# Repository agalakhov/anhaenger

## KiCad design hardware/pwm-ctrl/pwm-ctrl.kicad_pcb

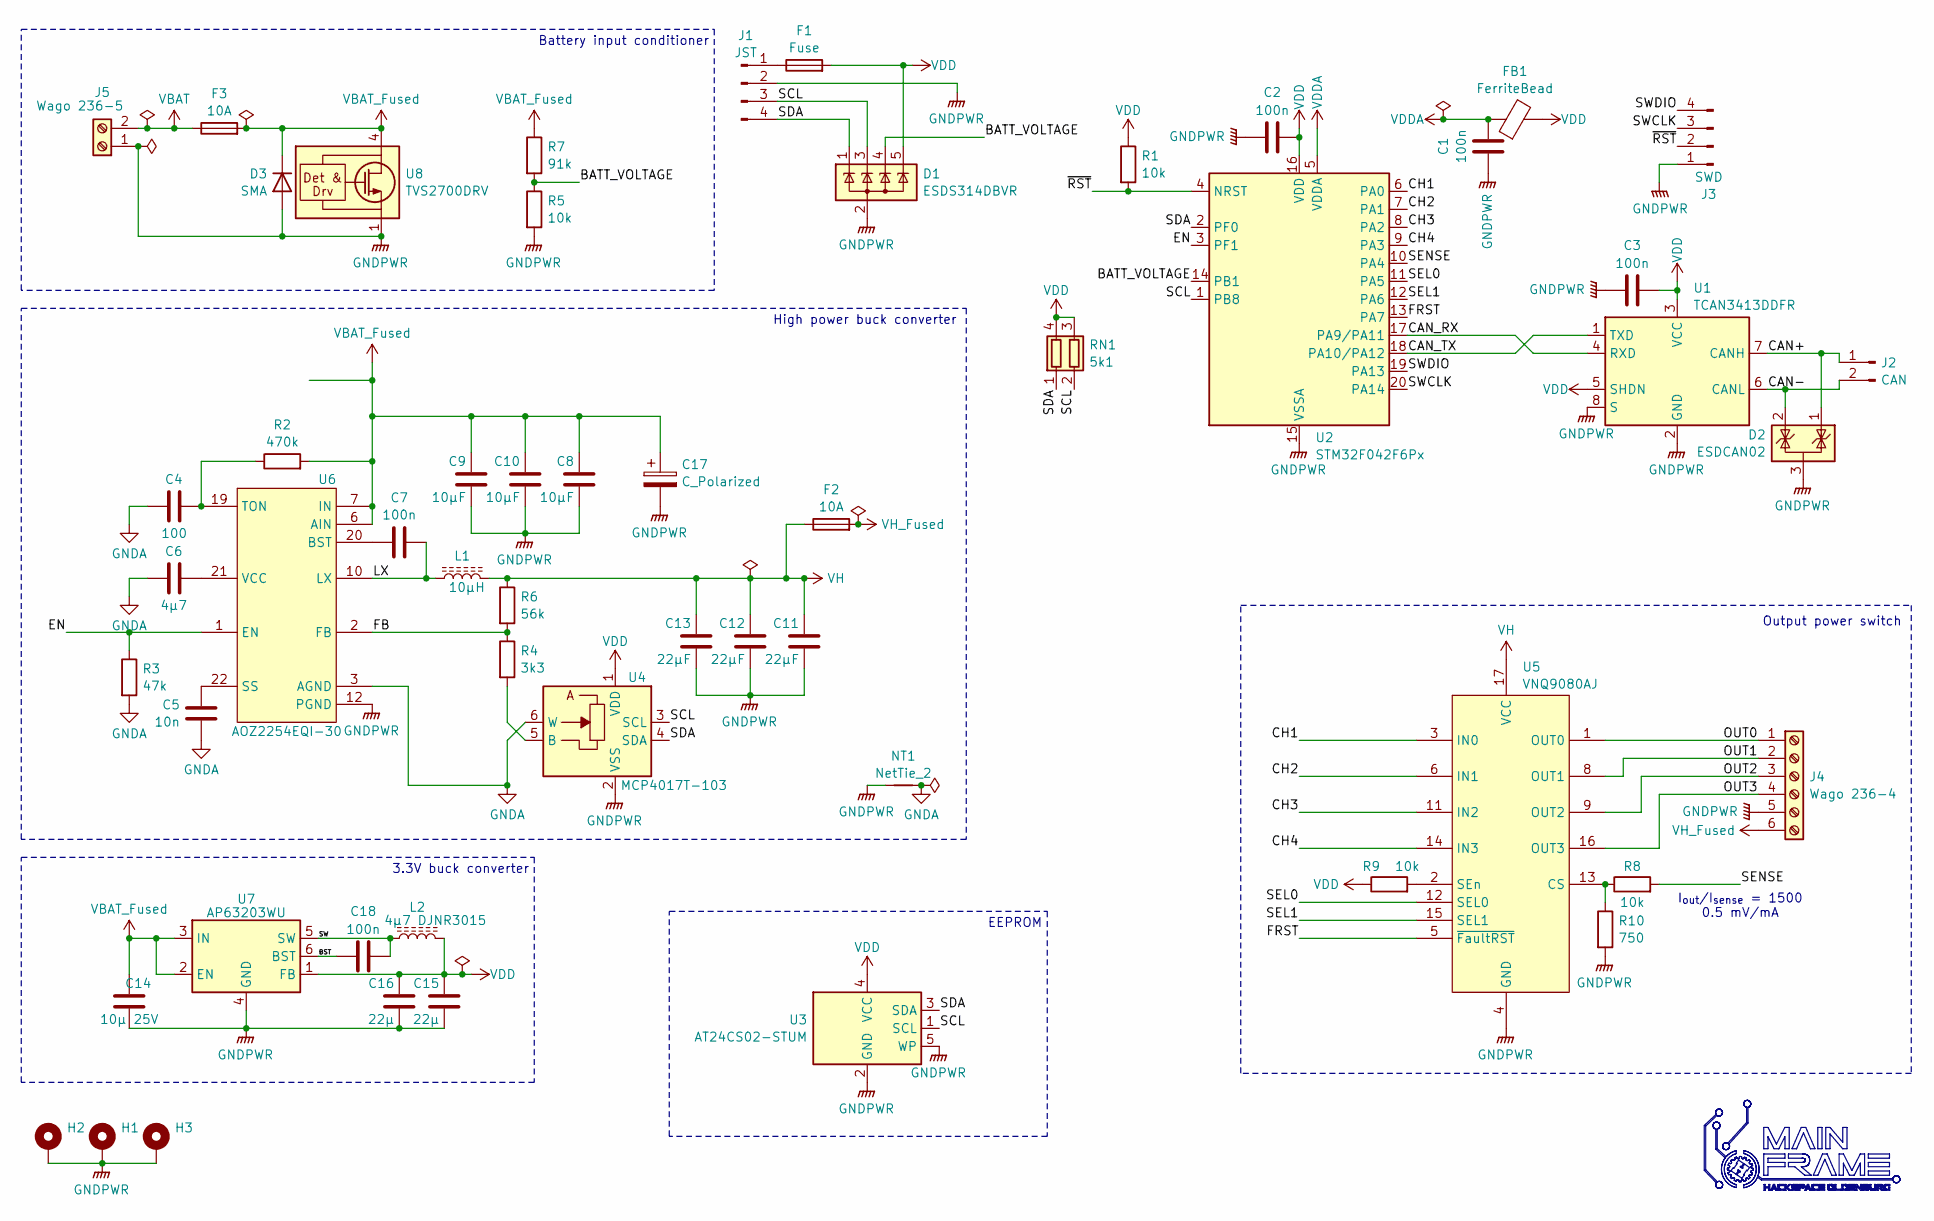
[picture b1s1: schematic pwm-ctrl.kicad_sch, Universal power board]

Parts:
C1, C2, C3, C18: 100n; C_0603_1608Metric
C4: 100; C_0603_1608Metric
C5: 10n; C_0603_1608Metric
C6: 4µ7; C_0805_2012Metric
C7: 100n; C_0805_2012Metric
C8, C9, C10: 10µF; C_1206_3216Metric
C11, C12, C13: 22µF; C_1206_3216Metric
C14: 10µ 25V; C_0805_2012Metric
C15, C16: 22µ; C_0805_2012Metric
C17: C_Polarized; CP_Elec_10x10.5
D1: ESDS314DBVR; SOT-23-5
D2: ESDCAN02; SOT-323_SC-70
D3: SMA; D_SMA
F1: Fuse; Fuse_0805_2012Metric
F2, F3: 10A; Fuseholder_Blade_Mini_Keystone_3568
FB1: FerriteBead; L_0603_1608Metric
H1, H2, H3: MountingHole_Pad_MP; MountingHole_3.2mm_M3_ISO7380_Pad_TopBottom
J1: JST; JST_XH_B4B-XH-A_1x04_P2.50mm_Vertical
J2: CAN; Wago_734-132_1x02_P3.50mm_Vertical
J3: SWD; PinHeader_1x04_P1.27mm_Vertical
J4: Wago 236-4; TerminalBlock_WAGO_236-406_1x06_P5.00mm_45Degree
J5: Wago 236-5; TerminalBlock_WAGO_236-502_1x02_P7.50mm_45Degree
L1: 10µH; L_TaiTech_TMPC1265_13.5x12.5mm
L2: 4µ7 DJNR3015; L_Neosid_SMS-ME3015
NT1: NetTie_2; NetTie-2_SMD_Pad0.5mm
R1, R5, R8, R9: 10k; R_0603_1608Metric
R2: 470k; R_0603_1608Metric
R3: 47k; R_0603_1608Metric
R4: 3k3; R_0603_1608Metric
R6: 56k; R_0603_1608Metric
R7: 91k; R_0603_1608Metric
R10: 750; R_0603_1608Metric
RN1: 5k1; R_Array_Convex_2x0603
U1: TCAN3413DDFR; TSOT-23-8
U2: STM32F042F6Px; TSSOP-20_4.4x6.5mm_P0.65mm
U3: AT24CS02-STUM; SOT-353_SC-70-5
U4: MCP4017T-103; SOT-363_SC-70-6
U5: VNQ9080AJ; PowerSSO-16-1EP_3.9x4.9mm_P0.5mm_EP2.5x3.61mm_ThermalVias
U6: AOZ2254EQI-30; AOZ_QFN-22_2EP_4x4mm_P0.5mm
U7: AP63203WU; TSOT-23-6
U8: TVS2700DRV; WSON-6-1EP_2x2mm_P0.65mm_EP1x1.6mm

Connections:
/BATT_VOLTAGE: D1.4 (K), R5.1, R7.2, U2.14 (PB1)
/BST: C18.1, U7.6 (BST)
/CAN+: D2.1 (K), J2.1, U1.7 (CANH)
/CAN-: D2.2 (K), J2.2, U1.6 (CANL)
/CAN_RX: U1.4 (RXD), U2.17 (PA9/PA11)
/CAN_TX: U1.1 (TXD), U2.18 (PA10/PA12)
/CH1: U2.6 (PA0), U5.3 (IN0)
/CH2: U2.7 (PA1), U5.6 (IN1)
/CH3: U2.8 (PA2), U5.11 (IN2)
/CH4: U2.9 (PA3), U5.14 (IN3)
/EN: R3.1, U2.3 (PF1), U6.1 (EN)
/FB: R4.1, R6.2, U6.2 (FB)
/FRST: U2.13 (PA7), U5.5 (~FaultRST)
/LX: C7.2, L1.1, U6.10 (LX), U6.11 (LX), U6.16 (LX), U6.17 (LX), U6.18 (LX), U6.EP2 (LX)
/OUT0: J4.1, U5.1 (OUT0)
/OUT1: J4.2, U5.8 (OUT1)
/OUT2: J4.3, U5.9 (OUT2)
/OUT3: J4.4, U5.16 (OUT3)
/SCL: D1.3 (K), J1.3, RN1.2 (R2.1), U2.1 (PB8), U3.1 (SCL), U4.3 (SCL)
/SDA: D1.1 (K), J1.4, RN1.1 (R1.1), U2.2 (PF0), U3.3 (SDA), U4.4 (SDA)
/SEL0: U2.11 (PA5), U5.12 (SEL0)
/SEL1: U2.12 (PA6), U5.15 (SEL1)
/SENSE: R8.2, U2.10 (PA4)
/SW: C18.2, L2.1, U7.5 (SW)
/SWCLK: J3.3, U2.20 (PA14)
/SWDIO: J3.4, U2.19 (PA13)
/~RST: J3.2, R1.2, U2.4 (NRST)
GNDA: C4.2, C5.1, C6.2, NT1.2, R3.2, U4.6 (W), U6.3 (AGND)
GNDPWR: C1.1, C2.1, C3.1, C8.1, C9.1, C10.1, C11.1, C12.1, C13.1, C14.1, C15.1, C16.1, C17.2, D1.2 (A), D2.3 (A), D3.2 (A), H1.1, H2.1, H3.1, J1.2, J3.1, J4.5, J5.1, NT1.1, R5.2, R10.2, U1.2 (GND), U1.8 (S), U2.15 (VSSA), U3.2 (GND), U3.5 (WP), U4.2 (VSS), U5.4 (GND), U6.12 (PGND), U6.13 (PGND), U6.14 (PGND), U6.15 (PGND), U7.4 (GND), U8.1 (GND), U8.2 (GND), U8.3 (GND), U8.7 (GND)
unnamed: F1.1, J1.1
unnamed: R4.2, U4.5 (B)
unnamed: R8.1, R10.1, U5.13 (CS)
unnamed: R9.2, U5.2 (SEn)
unnamed: C7.1, U6.20 (BST)
unnamed: C5.2, U6.22 (SS)
unnamed: C4.1, R2.1, U6.19 (TON)
unnamed: C6.1, U6.21 (VCC)
VBAT: F3.1, J5.2
VBAT_Fused: C8.2, C9.2, C10.2, C14.2, C17.1, D3.1 (K), F3.2, R2.2, R7.1, U6.6 (AIN), U6.7 (IN), U6.8 (IN), U6.9 (IN), U6.EP1 (IN), U7.2 (EN), U7.3 (IN), U8.4 (IN), U8.5 (IN), U8.6 (IN)
VDD: C2.2, C3.2, C15.2, C16.2, D1.5 (K), F1.2, FB1.2, L2.2, R1.1, R9.1, RN1.3 (R2.2), RN1.4 (R1.2), U1.3 (VCC), U1.5 (SHDN), U2.16 (VDD), U3.4 (VCC), U4.1 (VDD), U7.1 (FB)
VDDA: C1.2, FB1.1, U2.5 (VDDA)
VH: C11.2, C12.2, C13.2, F2.1, L1.2, R6.1, U5.17 (VCC)
VH_Fused: F2.2, J4.6

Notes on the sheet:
EEPROM
Battery input conditioner
High power buck converter
Output power switch
I_{out}/I_{sense} = 1500 0.5 mV/mA
3.3V buck converter

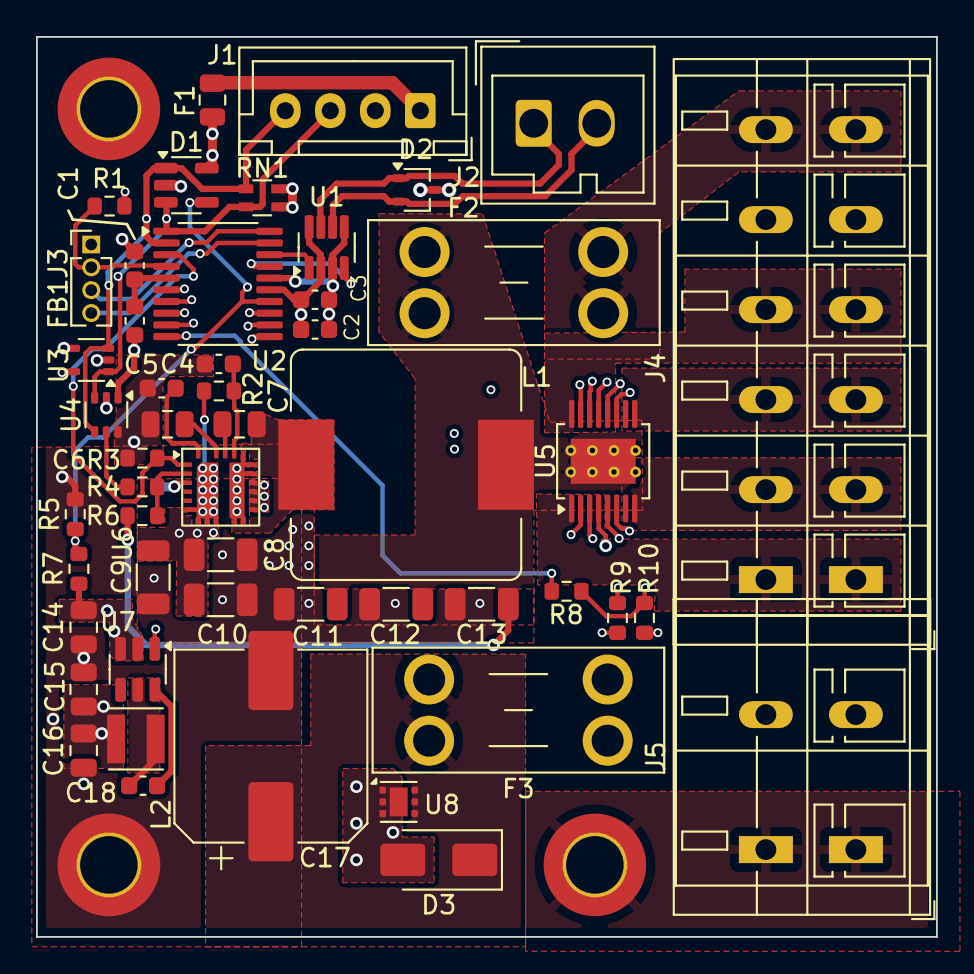
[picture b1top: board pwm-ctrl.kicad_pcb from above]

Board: 4 copper layers, 50.0 x 50.0 mm, 55 parts (1 on the bottom side), 43 nets.

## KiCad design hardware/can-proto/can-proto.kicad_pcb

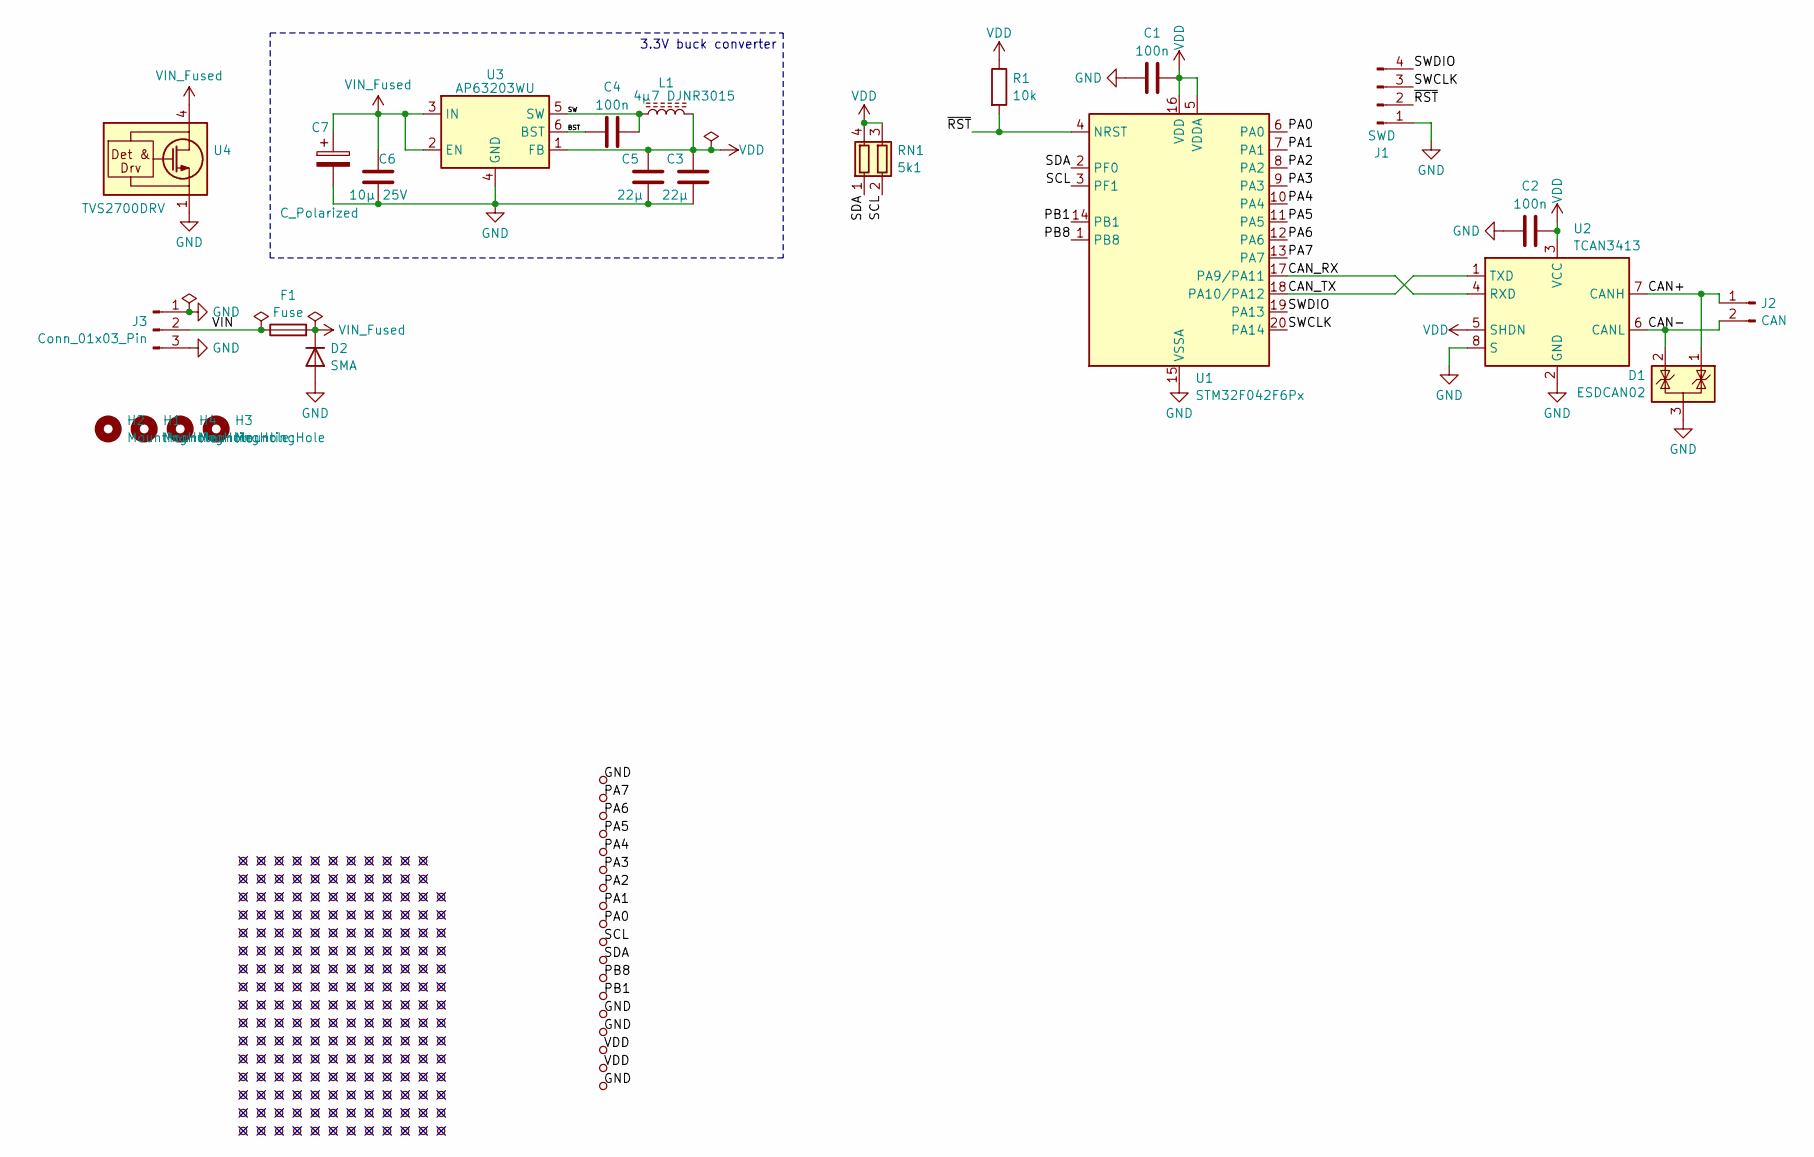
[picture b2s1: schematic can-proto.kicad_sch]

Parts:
C1, C2, C4: 100n; C_0603_1608Metric
C3, C5: 22µ; C_0805_2012Metric
C6: 10µ 25V; C_0805_2012Metric
C7: C_Polarized; CP_Elec_6.3x5.7
D1: ESDCAN02; SOT-323_SC-70
D2: SMA; D_SMA
F1: Fuse; Fuse_1206_3216Metric
H1, H2, H3, H4: MountingHole; MountingHole_3.2mm_M3_ISO14580
J1: SWD; PinHeader_1x04_P1.27mm_Vertical
J2: CAN; Wago_734-132_1x02_P3.50mm_Vertical
J3: Conn_01x03_Pin; Wago_734-133_1x03_P3.50mm_Vertical
L1: 4µ7 DJNR3015; L_Neosid_SMS-ME3015
R1: 10k; R_0603_1608Metric
RN1: 5k1; R_Array_Convex_2x0603
TP1, TP2, TP3, TP4, TP5, TP6, TP7, TP8, TP9, TP10, TP11, TP12, TP13, TP14, TP15, TP16, TP17, TP18, TP19, TP20, TP21, TP22, TP23, TP24, TP25, TP26, TP27, TP28, TP29, TP30, TP31, TP32, TP33, TP34, TP35, TP36, TP37, TP38, TP39, TP40, TP41, TP42, TP43, TP44, TP45, TP46, TP47, TP48, TP49, TP50, TP51, TP52, TP53, TP54, TP55, TP56, TP57, TP58, TP59, TP60, TP61, TP62, TP63, TP64, TP65, TP66, TP67, TP68, TP69, TP70, TP71, TP72, TP73, TP74, TP75, TP76, TP77, TP78, TP79, TP80, TP81, TP82, TP83, TP84, TP85, TP86, TP87, TP88, TP89, TP90, TP91, TP92, TP93, TP94, TP95, TP96, TP97, TP98, TP99, TP100, TP101, TP102, TP103, TP104, TP105, TP106, TP107, TP108, TP109, TP110, TP111, TP112, TP113, TP114, TP115, TP116, TP117, TP118, TP119, TP120, TP121, TP122, TP123, TP124, TP125, TP126, TP127, TP128, TP129, TP130, TP131, TP132, TP133, TP134, TP135, TP136, TP137, TP138, TP139, TP140, TP141, TP142, TP143, TP144, TP145, TP146, TP147, TP148, TP149, TP150, TP151, TP152, TP153, TP154, TP155, TP156, TP157, TP158, TP159, TP160, TP161, TP162, TP163, TP164, TP165, TP166, TP167, TP168, TP169, TP170, TP171, TP172, TP173, TP174, TP175, TP176, TP177, TP178, TP179, TP180, TP181, TP182, TP183, TP184, TP185, TP186, TP187, TP188, TP189, TP190, TP191, TP192, TP193, TP194, TP195, TP196, TP197, TP198, TP199, TP200, TP201, TP202, TP203, TP204, TP205, TP206, TP207, TP208: TestPoint_Small; PTH_Hole_0.8mm
U1: STM32F042F6Px; TSSOP-20_4.4x6.5mm_P0.65mm
U2: TCAN3413; TSOT-23-8
U3: AP63203WU; TSOT-23-6
U4: TVS2700DRV; WSON-6-1EP_2x2mm_P0.65mm_EP1x1.6mm

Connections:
/BST: C4.1, U3.6 (BST)
/CAN+: D1.1 (K), J2.1, U2.7 (CANH)
/CAN-: D1.2 (K), J2.2, U2.6 (CANL)
/CAN_RX: U1.17 (PA9/PA11), U2.4 (RXD)
/CAN_TX: U1.18 (PA10/PA12), U2.1 (TXD)
/PA0: TP93.1, U1.6 (PA0)
/PA1: TP81.1, U1.7 (PA1)
/PA2: TP69.1, U1.8 (PA2)
/PA3: TP57.1, U1.9 (PA3)
/PA4: TP45.1, U1.10 (PA4)
/PA5: TP33.1, U1.11 (PA5)
/PA6: TP21.1, U1.12 (PA6)
/PA7: TP11.1, U1.13 (PA7)
/PB1: TP141.1, U1.14 (PB1)
/PB8: TP129.1, U1.1 (PB8)
/SCL: RN1.2 (R2.1), TP105.1, U1.3 (PF1)
/SDA: RN1.1 (R1.1), TP117.1, U1.2 (PF0)
/SW: C4.2, L1.1, U3.5 (SW)
/SWCLK: J1.3, U1.20 (PA14)
/SWDIO: J1.4, U1.19 (PA13)
/VIN: F1.1, J3.2
/~RST: J1.2, R1.2, U1.4 (NRST)
GND: C1.1, C2.1, C3.1, C5.1, C6.1, C7.2, D1.3 (A), D2.2 (A), J1.1, J3.1, J3.3, TP1.1, TP153.1, TP165.1, TP199.1, U1.15 (VSSA), U2.2 (GND), U2.8 (S), U3.4 (GND), U4.1 (GND), U4.2 (GND), U4.3 (GND), U4.7 (GND)
VDD: C1.2, C2.2, C3.2, C5.2, L1.2, R1.1, RN1.3 (R2.2), RN1.4 (R1.2), TP177.1, TP189.1, U1.5 (VDDA), U1.16 (VDD), U2.3 (VCC), U2.5 (SHDN), U3.1 (FB)
VIN_Fused: C6.2, C7.1, D2.1 (K), F1.2, U3.2 (EN), U3.3 (IN), U4.4 (IN), U4.5 (IN), U4.6 (IN)

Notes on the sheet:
3.3V buck converter

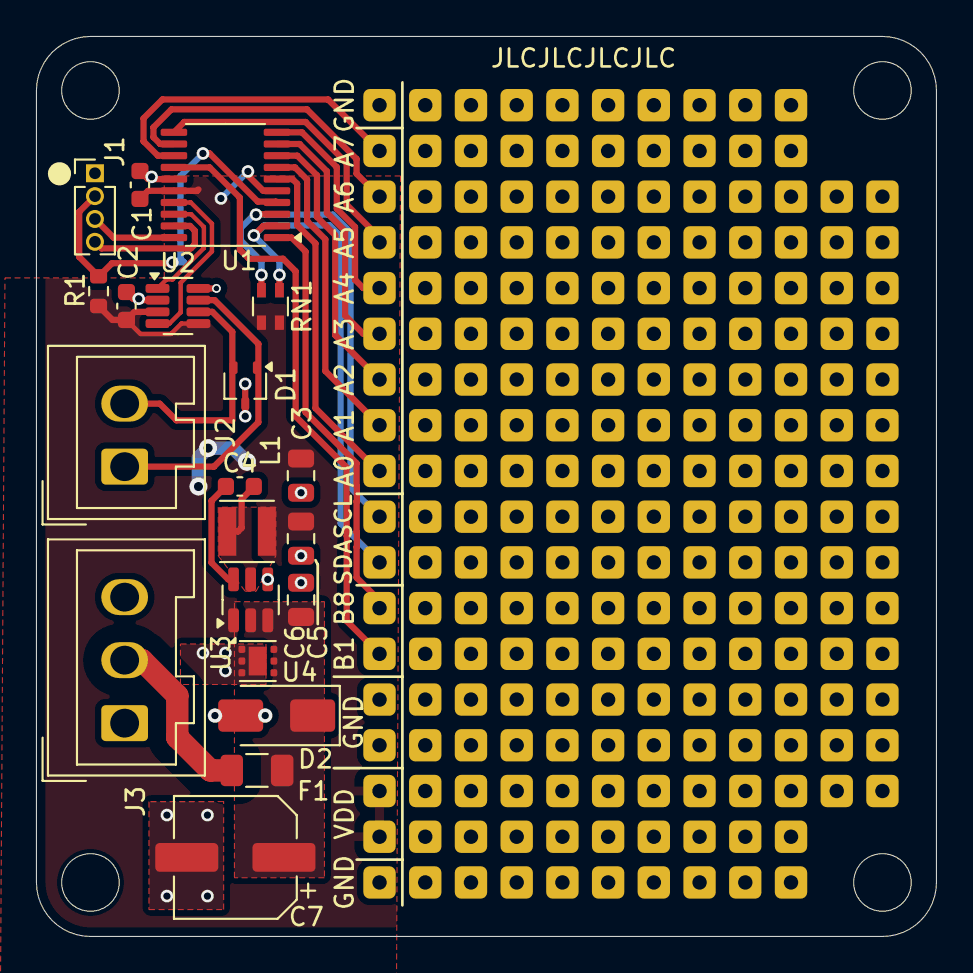
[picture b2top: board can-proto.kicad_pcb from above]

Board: 2 copper layers, 50.0 x 50.0 mm, 232 parts (0 on the bottom side), 25 nets.

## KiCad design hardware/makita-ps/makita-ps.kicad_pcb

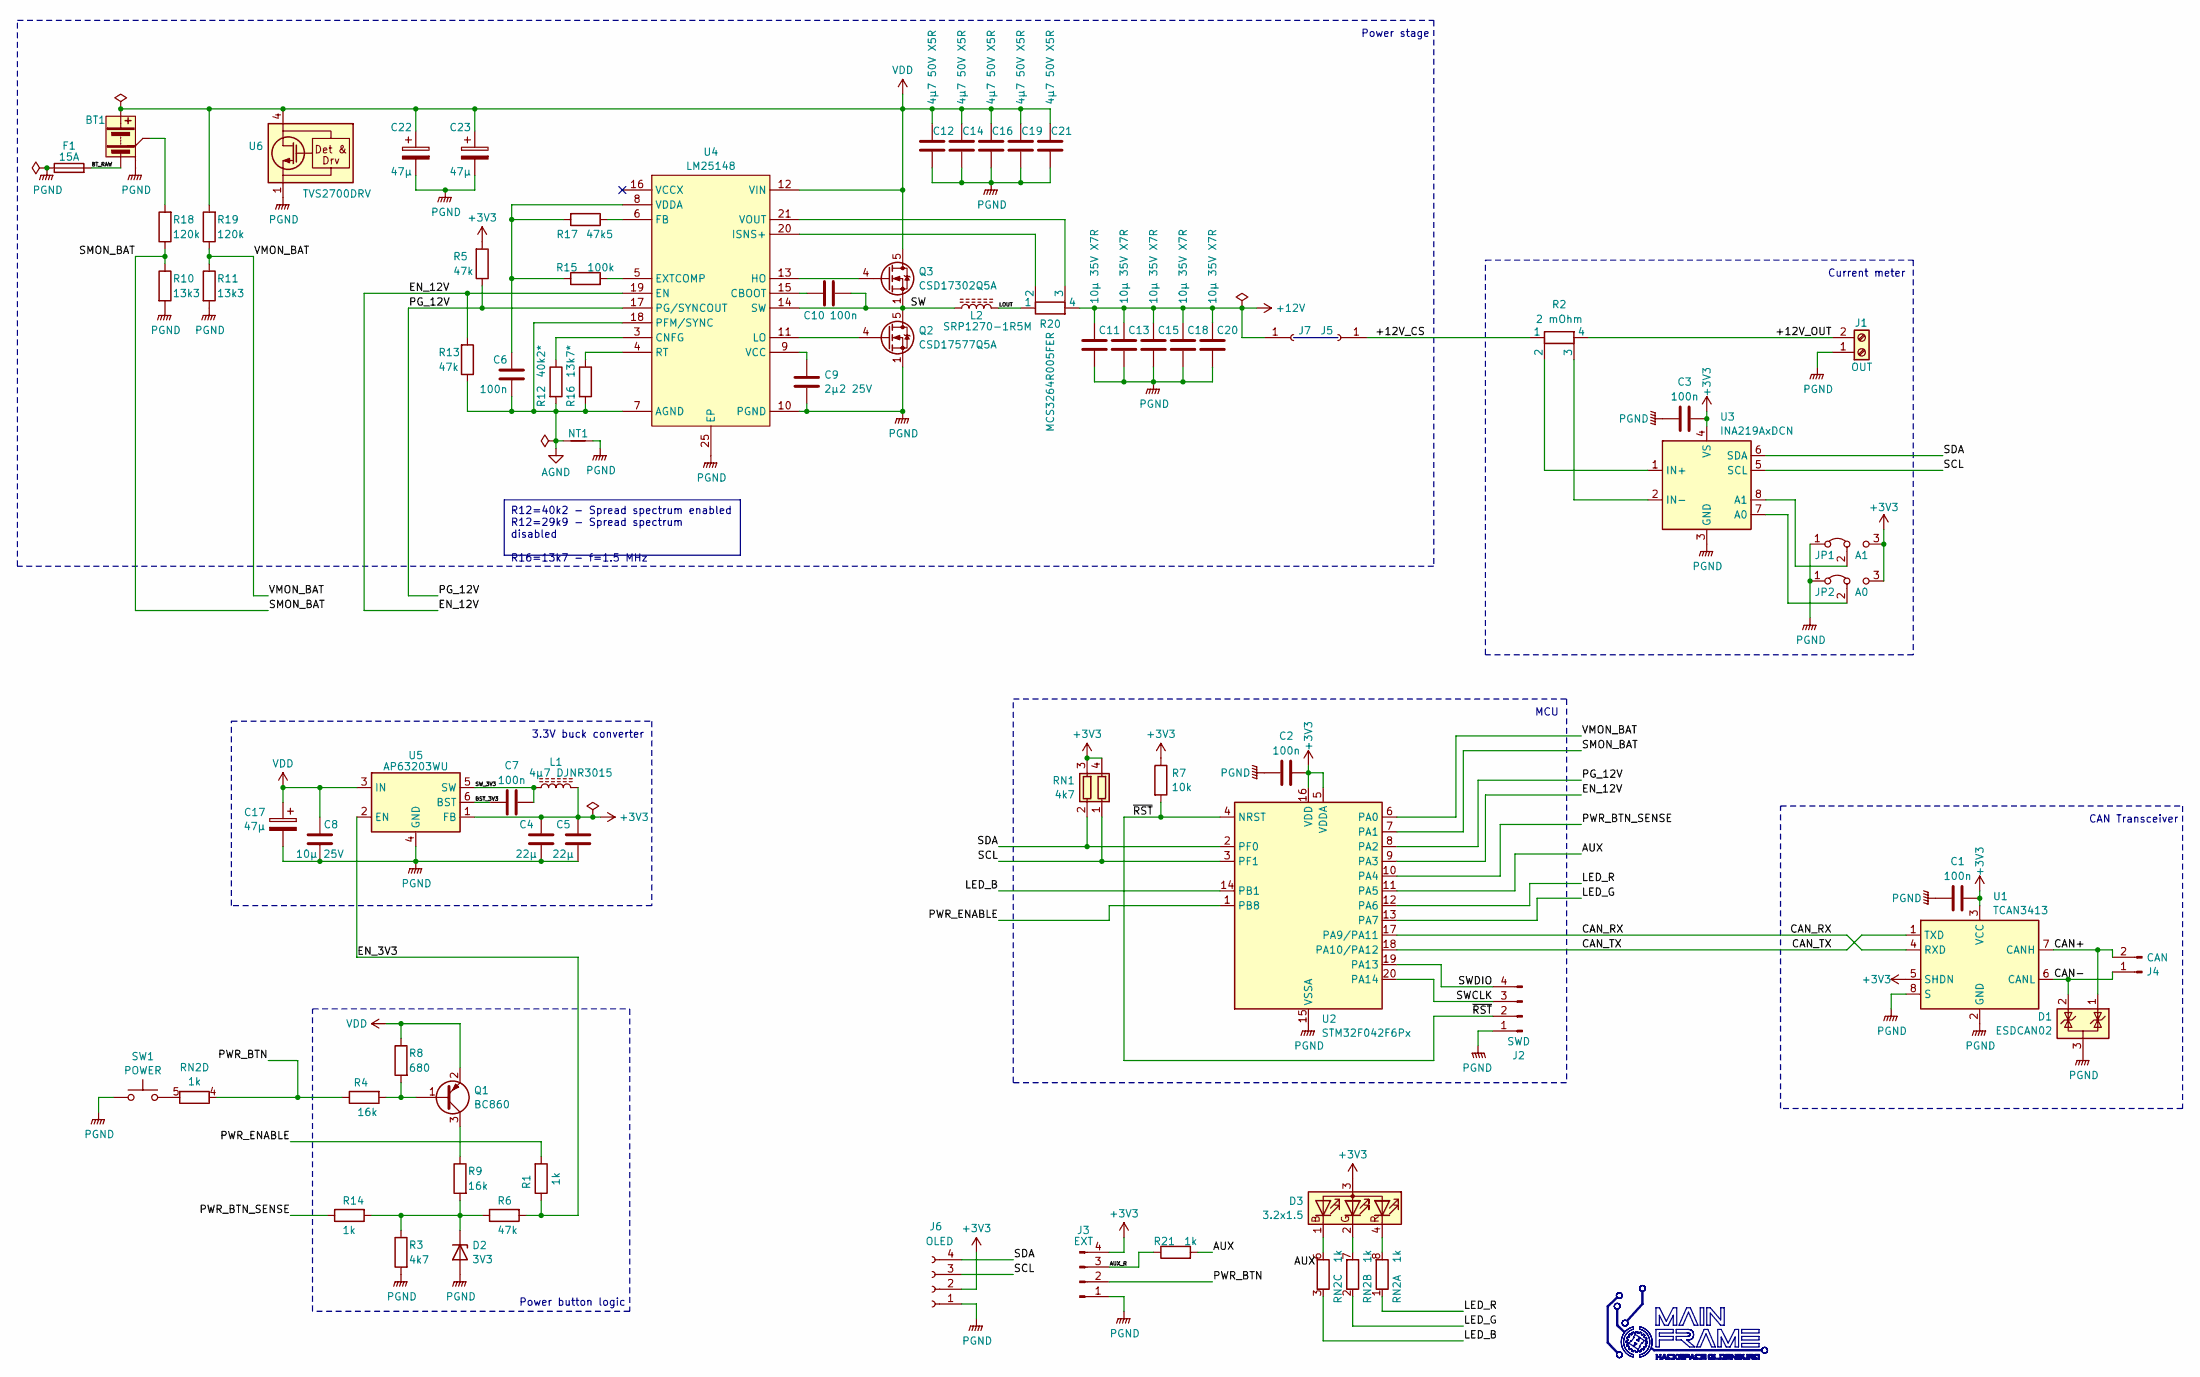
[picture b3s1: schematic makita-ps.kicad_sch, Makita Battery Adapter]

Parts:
BT1: Makita Battery
C1, C2, C3, C7: 100n; C_0603_1608Metric
C4, C5: 22µ; C_0805_2012Metric
C6, C10: 100n; C_0805_2012Metric
C8: 10µ 25V; C_0805_2012Metric
C9: 2µ2 25V; C_0805_2012Metric
C11, C13, C15, C18, C20: 10µ 35V X7R; C_1206_3216Metric
C12, C14, C16, C19, C21: 4µ7 50V X5R; C_0805_2012Metric
C17, C22, C23: 47µ; CP_Elec_6.3x5.4
D1: ESDCAN02; SOT-323_SC-70
D2: 3V3; D_SOD-323
D3: 3.2x1.5; LED_RGB_Xinglight_XL3210RGBC_Horizontal
F1: 15A; FUSE_3587-15
J1: OUT; PhoenixContact_MSTBA_2,5_2-G-5,08_1x02_P5.08mm_Horizontal
J2: SWD; PinHeader_1x04_P1.27mm_Horizontal
J3: EXT; JST_XH_S4B-XH-A_1x04_P2.50mm_Horizontal
J4: CAN; PhoenixContact_MC_1,5_2-G-3.5_1x02_P3.50mm_Horizontal
J5, J7: Conn_01x01_Socket; SolderWire-2sqmm_1x01_D2mm_OD3.9mm
J6: OLED; PinSocket_1x04_P2.54mm_Vertical
JP1: A1; SolderJumper-3_P2.0mm_Open_TrianglePad1.0x1.5mm_NumberLabels
JP2: A0; SolderJumper-3_P2.0mm_Open_TrianglePad1.0x1.5mm_NumberLabels
L1: 4µ7 DJNR3015; L_Neosid_SMS-ME3015
L2: SRP1270-1R5M; L_Bourns_SRP1245A
NT1: NetTie_2; NetTie-2_SMD_Pad0.5mm
Q1: BC860; SOT-23
Q2: CSD17577Q5A; LFPAK56
Q3: CSD17302Q5A; LFPAK56
R1, R14, R21: 1k; R_0603_1608Metric
R2: 2 mOhm; R_Shunt_Vishay_WSK2512_6332Metric_T2.21mm
R3: 4k7; R_0603_1608Metric
R4, R9: 16k; R_0603_1608Metric
R5, R6, R13: 47k; R_0603_1608Metric
R7: 10k; R_0603_1608Metric
R8: 680; R_0603_1608Metric
R10, R11: 13k3; R_0603_1608Metric
R12: 40k2*; R_0603_1608Metric
R15: 100k; R_0603_1608Metric
R16: 13k7*; R_0603_1608Metric
R17: 47k5; R_0603_1608Metric
R18, R19: 120k; R_0805_2012Metric
R20: MCS3264R005FER; R_Shunt_Vishay_WSK2512_6332Metric_T2.21mm
RN1: 4k7; R_Array_Convex_2x0603
RN2: 1k; R_Array_Convex_4x0603
SW1: POWER; SW_Tactile_SPST_Angled_PTS645Vx31-2LFS
U1: TCAN3413; TSOT-23-8
U2: STM32F042F6Px; TSSOP-20_4.4x6.5mm_P0.65mm
U3: INA219AxDCN; SOT-23-8
U4: LM25148; Texas_RGY_R-PVQFN-N24_EP2.05x3.1mm
U5: AP63203WU; TSOT-23-6
U6: TVS2700DRV; WSON-6-1EP_2x2mm_P0.65mm_EP1x1.6mm

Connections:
+3V3: C1.2, C2.2, C3.2, C4.2, C5.2, D3.3 (A), J3.4, J6.2, JP1.3 (B), JP2.3 (B), L1.2, R5.2, R7.1, RN1.3 (R2.2), RN1.4 (R1.2), U1.3 (VCC), U1.5 (SHDN), U2.5 (VDDA), U2.16 (VDD), U3.4 (VS), U5.1 (FB)
+12V: C11.1, C13.1, C15.1, C18.1, C20.1, J7.1, R20.4
/+12V_CS: J5.1, R2.1
/+12V_OUT: J1.2, R2.4
/AUX: R21.2, U2.11 (PA5)
/AUX_R: J3.3, R21.1
/BST_3V3: C7.1, U5.6 (BST)
/BT_RAW: BT1.-, F1.2
/CAN+: D1.1 (K), J4.2, U1.7 (CANH)
/CAN-: D1.2 (K), J4.1, U1.6 (CANL)
/CAN_RX: U1.4 (RXD), U2.17 (PA9/PA11)
/CAN_TX: U1.1 (TXD), U2.18 (PA10/PA12)
/EN_3V3: R1.1, R6.2, U5.2 (EN)
/EN_12V: R13.2, U2.9 (PA3), U4.19 (EN)
/LED_B: RN2.3 (R3.1), U2.14 (PB1)
/LED_G: RN2.2 (R2.1), U2.13 (PA7)
/LED_R: RN2.1 (R1.1), U2.12 (PA6)
/LOUT: L2.2, R20.1
/PG_12V: R5.1, U2.8 (PA2), U4.17 (PG/SYNCOUT)
/PWR_BTN: J3.2, R4.1, RN2.4 (R4.1)
/PWR_BTN_SENSE: R14.1, U2.10 (PA4)
/PWR_ENABLE: R1.2, U2.1 (PB8)
/SCL: J6.3, RN1.1 (R1.1), U2.3 (PF1), U3.5 (SCL)
/SDA: J6.4, RN1.2 (R2.1), U2.2 (PF0), U3.6 (SDA)
/SMON_BAT: R10.1, R18.1, U2.7 (PA1)
/SW: C10.2, L2.1, Q2.5 (D), Q3.1 (S), Q3.2 (S), Q3.3 (S), U4.14 (SW)
/SWCLK: J2.3, U2.20 (PA14)
/SWDIO: J2.4, U2.19 (PA13)
/SW_3V3: C7.2, L1.1, U5.5 (SW)
/VMON_BAT: R11.1, R19.1, U2.6 (PA0)
/~RST: J2.2, R7.2, U2.4 (NRST)
AGND: C6.2, NT1.1, R12.2, R13.1, R16.2, U4.7 (AGND), U4.18 (PFM/SYNC)
unnamed: BT1.T, R18.2
unnamed: D2.1 (K), R3.1, R6.1, R9.2, R14.2
unnamed: D3.1 (BK), RN2.6 (R3.2)
unnamed: D3.2 (GK), RN2.7 (R2.2)
unnamed: D3.4 (RK), RN2.8 (R1.2)
unnamed: JP1.2 (C), U3.8 (A1)
unnamed: JP2.2 (C), U3.7 (A0)
unnamed: Q1.1 (B), R4.2, R8.2
unnamed: Q1.3 (C), R9.1
unnamed: Q2.4 (G), U4.11 (LO)
unnamed: Q3.4 (G), U4.13 (HO)
unnamed: RN2.5 (R4.2), SW1.2
unnamed: R2.2, U3.1 (IN+)
unnamed: R2.3, U3.2 (IN-)
unnamed: C10.1, U4.15 (CBOOT)
unnamed: R12.1, U4.3 (CNFG)
unnamed: R15.2, U4.5 (EXTCOMP)
unnamed: R17.1, U4.6 (FB)
unnamed: R20.2, U4.20 (ISNS+)
unnamed: R16.1, U4.4 (RT)
unnamed: C9.1, U4.9 (VCC)
unnamed: C6.1, R15.1, R17.2, U4.8 (VDDA)
unnamed: R20.3, U4.21 (VOUT)
PGND: BT1.M, C1.1, C2.1, C3.1, C4.1, C5.1, C8.1, C9.2, C11.2, C12.2, C13.2, C14.2, C15.2, C16.2, C17.2, C18.2, C19.2, C20.2, C21.2, C22.2, C23.2, D1.3 (A), D2.2 (A), F1.1, J1.1, J2.1, J3.1, J6.1, JP1.1 (A), JP2.1 (A), NT1.2, Q2.1 (S), Q2.2 (S), Q2.3 (S), R3.2, R10.2, R11.2, SW1.1, U1.2 (GND), U1.8 (S), U2.15 (VSSA), U3.3 (GND), U4.1 (NC), U4.2 (NC), U4.10 (PGND), U4.22 (NC), U4.23 (NC), U4.24 (NC), U4.25 (EP), U5.4 (GND), U6.1 (GND), U6.2 (GND), U6.3 (GND), U6.7 (GND)
VDD: BT1.+, C8.2, C12.1, C14.1, C16.1, C17.1, C19.1, C21.1, C22.1, C23.1, Q1.2 (E), Q3.5 (D), R8.1, R19.2, U4.12 (VIN), U5.3 (IN), U6.4 (IN), U6.5 (IN), U6.6 (IN)

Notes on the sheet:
R12=40k2 - Spread spectrum enabled R12=29k9 - Spread spectrum disabled R16=13k7 - f=1.5 MHz
Power stage
MCU
Power button logic
CAN Transceiver
3.3V buck converter
Current meter

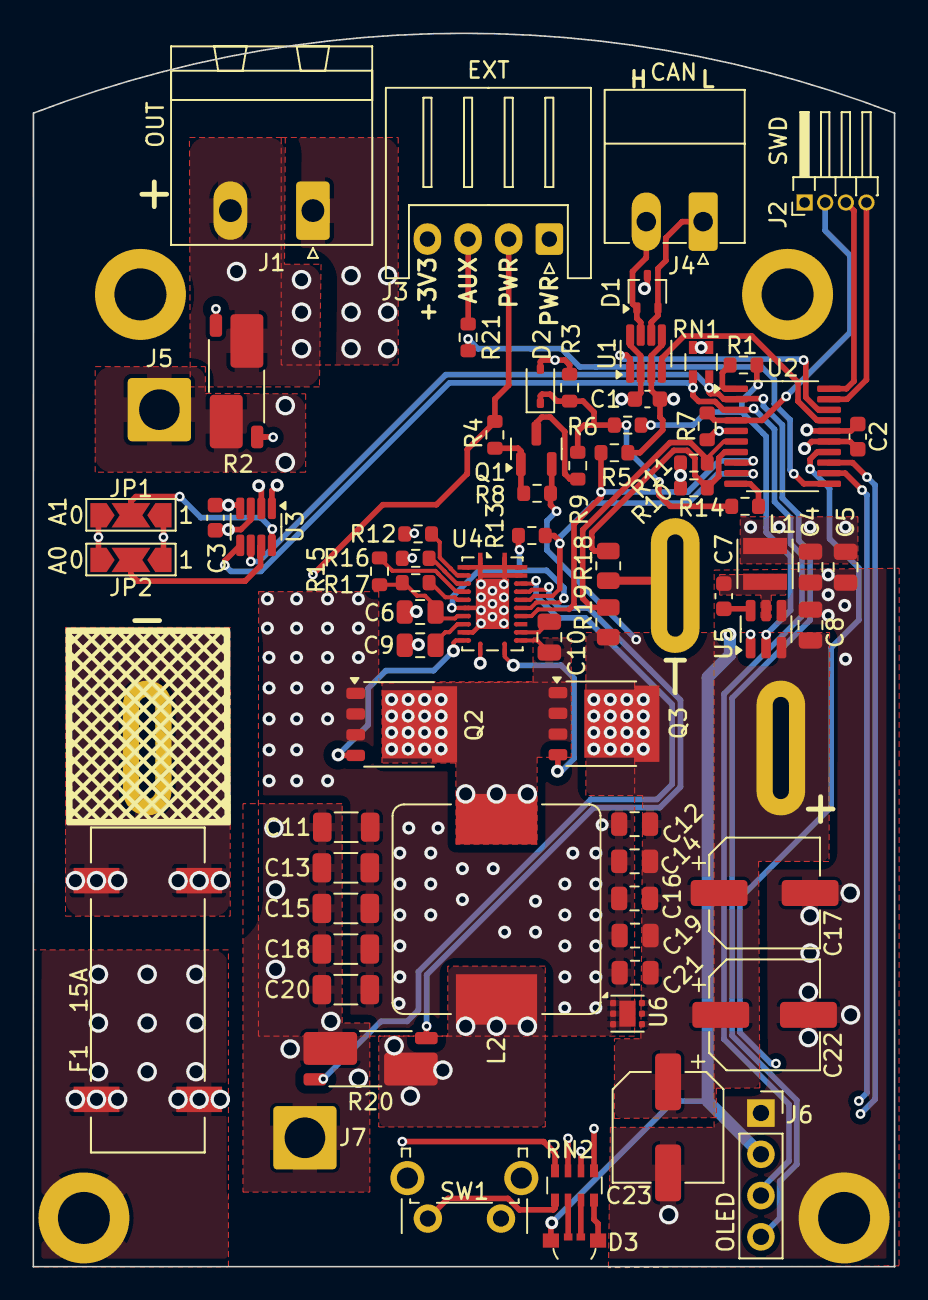
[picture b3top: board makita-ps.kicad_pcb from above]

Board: 4 copper layers, 53.0 x 75.9 mm, 73 parts (1 on the bottom side), 57 nets.

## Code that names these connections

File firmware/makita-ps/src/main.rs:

#![feature(impl_trait_in_assoc_type)]
#![no_std]
#![no_main]

mod adc;
mod can;
mod display;
mod led;
mod vmon;

use {defmt_rtt as _, panic_probe as _};

use crate::{
    adc::process as adc_process,
    can::process as can_process,
    display::process as display_process,
    led::{Color, Led},
    vmon::process as voltage_monitor_process,
};
use core::sync::atomic::{AtomicBool, Ordering};
use defmt::info;
use embassy_executor::{main, task, Spawner};
use embassy_futures::{join::join, select::select};
use embassy_stm32::{
    adc::{self as stm32_adc, Adc, AdcChannel},
    bind_interrupts,
    can::{self as stm32_can, Can},
    exti::ExtiInput,
    gpio::{Flex, Input, Level, Output, Pull, Speed},
    i2c::{self, mode::Master, I2c, Config as I2cConfig},
    mode::Async,
    pac, peripherals,
    time::khz,
    wdg::IndependentWatchdog,
    Config as DeviceConfig,
};
use embassy_sync::{blocking_mutex::raw::NoopRawMutex, mutex::Mutex};
use embassy_time::{Duration, Timer};
use static_cell::StaticCell;

bind_interrupts!(struct Irqs {
    I2C1 => i2c::EventInterruptHandler<peripherals::I2C1>, i2c::ErrorInterruptHandler<peripherals::I2C1>;
    ADC1 => stm32_adc::InterruptHandler<peripherals::ADC1>;
    CEC_CAN => stm32_can::Rx0InterruptHandler<peripherals::CAN>, stm32_can::Rx1InterruptHandler<peripherals::CAN>,
               stm32_can::TxInterruptHandler<peripherals::CAN>, stm32_can::SceInterruptHandler<peripherals::CAN>;
});

static WANT_12V: AtomicBool = AtomicBool::new(false);
static SHUTDOWN: AtomicBool = AtomicBool::new(false);

#[task]
async fn power_process(mut btn_sense: ExtiInput<'static>) {
    loop {
        btn_sense.wait_for_rising_edge().await;
        select(
            async {
                btn_sense.wait_for_low().await;
            },
            async {
                Timer::after(Duration::from_millis(1000)).await;
                SHUTDOWN.store(true, Ordering::Relaxed);
            },
        )
        .await;
    }
}

#[task]
async fn delayed_12v_on() {
    Timer::after(Duration::from_secs(1)).await;
    info!("Turning on 12V");
    WANT_12V.store(true, Ordering::Relaxed);
}

#[main]
async fn main(spawner: Spawner) {
    // HSI oscillator 12 MHz, 64 MHz system frequency
    let mut config = DeviceConfig::default();
    {
        use embassy_stm32::rcc::*;
        config.rcc.hsi = true;
        config.rcc.hse = None;
        config.rcc.pll = Some(Pll {
            src: PllSource::HSI,
            prediv: PllPreDiv::DIV1,
            mul: PllMul::MUL6,
        });
        config.rcc.sys = Sysclk::PLL1_P;
        config.rcc.ahb_pre = AHBPrescaler::DIV1;
        config.rcc.apb1_pre = APBPrescaler::DIV1;
    }
    let dev = embassy_stm32::init(config);

    // Reconfigure pins for CAN bus
    pac::SYSCFG.cfgr1().modify(|w| w.set_pa11_pa12_rmp(true));

    // Turn software power switch on now
    let mut pwr_enable = Flex::new(dev.PB8);
    pwr_enable.set_high();
    pwr_enable.set_as_output(Speed::Low);

    // Configure watchdog
    let mut dog = IndependentWatchdog::new(dev.IWDG, 100_000);
    dog.unleash();

    // RGB LED
    let mut led = Led::new(dev.PA6, dev.PA7, dev.PB1);
    led.set_color(Color::Magenta);

    // 12V control
    let pg_12v = Input::new(dev.PA2, Pull::Up);
    let mut en_12v = Output::new(dev.PA3, Level::Low, Speed::Low);

    // Power on-off switch
    let pwr_btn_sense = ExtiInput::new(dev.PA4, dev.EXTI4, Pull::Down);
    spawner.spawn(power_process(pwr_btn_sense)).unwrap();
    dog.pet();

    // ADC for battery monitoring
    // VMON_BAT PA0
    // SMON_BAT PA1
    let adc = Adc::new(dev.ADC1, Irqs);
    spawner
        .spawn(adc_process(
            adc,
            dev.PA0.degrade_adc(),
            dev.PA1.degrade_adc(),
        ))
        .unwrap();

    // AUX PA5
    // CAN_RX PA9/PA11
    // CAN_TX PA10/PA12

    // I²C bus
    let scl = dev.PF1;
    let sda = dev.PF0;
    let i2c = I2c::new(
        dev.I2C1,
        scl,
        sda,
        Irqs,
        dev.DMA1_CH2,
        dev.DMA1_CH3,
        {
            let mut cfg = I2cConfig::default();
            cfg.frequency = khz(400);
            cfg
        },
    );
    static I2C_BUS: StaticCell<Mutex<NoopRawMutex, I2c<'_, Async, Master>>> = StaticCell::new();
    let i2c = Mutex::new(i2c);
    let i2c = I2C_BUS.init(i2c);

    spawner.spawn(voltage_monitor_process(i2c)).unwrap();
    dog.pet();

    spawner.spawn(display_process(i2c)).unwrap();
    dog.pet();

    let can = Can::new(dev.CAN, dev.PA11, dev.PA12, Irqs);
    spawner.spawn(can_process(can)).unwrap();

    info!("System startup");
    spawner.spawn(delayed_12v_on()).unwrap();
    while !SHUTDOWN.load(Ordering::Relaxed) {
        if pg_12v.is_low() {
            led.set_color(Color::Blue);
        } else {
            led.set_color(Color::Green);
        }

        if WANT_12V.load(Ordering::Relaxed) {
            en_12v.set_high();
        } else {
            en_12v.set_low();
        }

        dog.pet();
        Timer::after(Duration::from_millis(1)).await;
    }

    info!("Powering down");
    join(
        async {
            for _ in 0..3 {
                led.set_color(Color::Red);
                Timer::after(Duration::from_millis(150)).await;
                led.set_color(Color::Off);
                Timer::after(Duration::from_millis(150)).await;
            }
            pwr_enable.set_as_input(Pull::None);
        },
        async {
            loop {
                dog.pet();
                Timer::after_millis(10).await;
            }
        },
    )
    .await;
}

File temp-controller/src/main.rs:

#![feature(impl_trait_in_assoc_type)]
#![no_std]
#![no_main]

mod adc;
mod temperature;
mod can;

use {defmt_rtt as _, panic_probe as _};

use crate::{adc::process as adc_process, temperature::process as temperature_process, can::process as can_process};
use core::{
    cell::RefCell,
    sync::atomic::{AtomicBool, Ordering},
};
use defmt::{info, unwrap};
use embassy_embedded_hal::shared_bus::asynch::i2c::I2cDevice;
use embassy_executor::{main, task, Spawner};
use embassy_futures::select::select;
use embassy_stm32::{
    pac,
    adc::{self as stm32_adc, Adc, AdcChannel},
    bind_interrupts,
    can::{self as stm32_can, Can},
    exti::ExtiInput,
    gpio::{Flex, Input, Level, Output, OutputType, Pull, Speed},
    i2c::{self, I2c, Config as I2cConfig},
    mode::Async,
    peripherals,
    time::{khz, mhz},
    timer::{
        low_level::{CountingMode, OutputPolarity},
        simple_pwm::{PwmPin, SimplePwm},
    },
    wdg::IndependentWatchdog,
    Config as DeviceConfig,
};
use embassy_sync::{blocking_mutex::raw::NoopRawMutex, mutex::Mutex};
use embassy_time::Timer;
use num_traits::float::FloatCore;
use pid::Pid;
use static_cell::StaticCell;

bind_interrupts!(struct Irqs {
    I2C1 => i2c::EventInterruptHandler<peripherals::I2C1>, i2c::ErrorInterruptHandler<peripherals::I2C1>;
    ADC1 => stm32_adc::InterruptHandler<peripherals::ADC1>;
    CEC_CAN => stm32_can::Rx0InterruptHandler<peripherals::CAN>, stm32_can::Rx1InterruptHandler<peripherals::CAN>,
               stm32_can::TxInterruptHandler<peripherals::CAN>, stm32_can::SceInterruptHandler<peripherals::CAN>;
});

#[main]
async fn main(spawner: Spawner) {
    // HSI oscillator 12 MHz, 64 MHz system frequency
    let mut config = DeviceConfig::default();
    {
        use embassy_stm32::rcc::*;
        config.rcc.hsi = true;
        config.rcc.hse = None;
        config.rcc.pll = Some(Pll {
            src: PllSource::HSI,
            prediv: PllPreDiv::DIV1,
            mul: PllMul::MUL6,
        });
        config.rcc.sys = Sysclk::PLL1_P;
        config.rcc.ahb_pre = AHBPrescaler::DIV1;
        config.rcc.apb1_pre = APBPrescaler::DIV1;
    }
    let dev = embassy_stm32::init(config);

    // Reconfigure pins for CAN bus
    pac::SYSCFG.cfgr1().modify(|w| w.set_pa11_pa12_rmp(true));

    let sda = dev.PF0;
    let scl = dev.PB8;
    let i2c = I2c::new(
        dev.I2C1,
        scl,
        sda,
        Irqs,
        dev.DMA1_CH2,
        dev.DMA1_CH3,
        {
            let mut cfg = I2cConfig::default();
            cfg.frequency = khz(400);
            cfg
        },
    );

    let ch0 = PwmPin::new(dev.PA0, OutputType::PushPull);
    let ch1 = PwmPin::new(dev.PA1, OutputType::PushPull);
    let ch2 = PwmPin::new(dev.PA2, OutputType::PushPull);
    let ch3 = PwmPin::new(dev.PA3, OutputType::PushPull);

    let sel0 = Output::new(dev.PA5, Level::Low, Speed::Low);
    let sel1 = Output::new(dev.PA6, Level::Low, Speed::Low);
    let sels = [sel0, sel1];
    let frst = Output::new(dev.PA7, Level::High, Speed::Low);

    let adc = Adc::new(dev.ADC1, Irqs);
    unwrap!(spawner.spawn(adc_process(adc, dev.PA4.degrade_adc(), sels,)));

    unwrap!(spawner.spawn(temperature_process(i2c)));

    let can = Can::new(dev.CAN, dev.PA11, dev.PA12, Irqs);
    unwrap!(spawner.spawn(can_process(can)));

    let pwm = SimplePwm::new(
        dev.TIM2,
        Some(ch0),
        Some(ch1),
        Some(ch2),
        Some(ch3),
        khz(1),
        CountingMode::EdgeAlignedUp,
    );
    let mut pwm = pwm.split();

    pwm.ch1.set_polarity(OutputPolarity::ActiveHigh);
    pwm.ch2.set_polarity(OutputPolarity::ActiveHigh);
    pwm.ch3.set_polarity(OutputPolarity::ActiveHigh);
    pwm.ch4.set_polarity(OutputPolarity::ActiveHigh);
    pwm.ch1.set_duty_cycle_fully_off();
    pwm.ch2.set_duty_cycle_fully_off();
    pwm.ch3.set_duty_cycle_fully_off();
    pwm.ch4.set_duty_cycle_fully_off();
    pwm.ch1.enable();
    pwm.ch2.enable();
    pwm.ch3.enable();
    pwm.ch4.enable();

    let mut pid = Pid::<f32>::new(20.0, 100.0);
    pid.p(10.0, 100.0).i(0.1, 50.0).d(0.1, 10.0);

    loop {
        Timer::after_millis(100).await;
        let t = temperature::TEMPERATURE.load(Ordering::Relaxed) as f32 / 10.0;
        let v = pid.next_control_output(t);

        let duty = (-v.output).clamp(0.0, 100.0);
        info!("PWM duty {}", duty);

        pwm.ch1
            .set_duty_cycle_fraction((duty * 100.0).round() as u16, 10000);
    }
}

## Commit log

2025-08-19 Converted to workspace
2025-08-21 Support temperature display on the test board
2025-08-21 Move sources to subdirectory
2025-08-21 Add hardware schematics
